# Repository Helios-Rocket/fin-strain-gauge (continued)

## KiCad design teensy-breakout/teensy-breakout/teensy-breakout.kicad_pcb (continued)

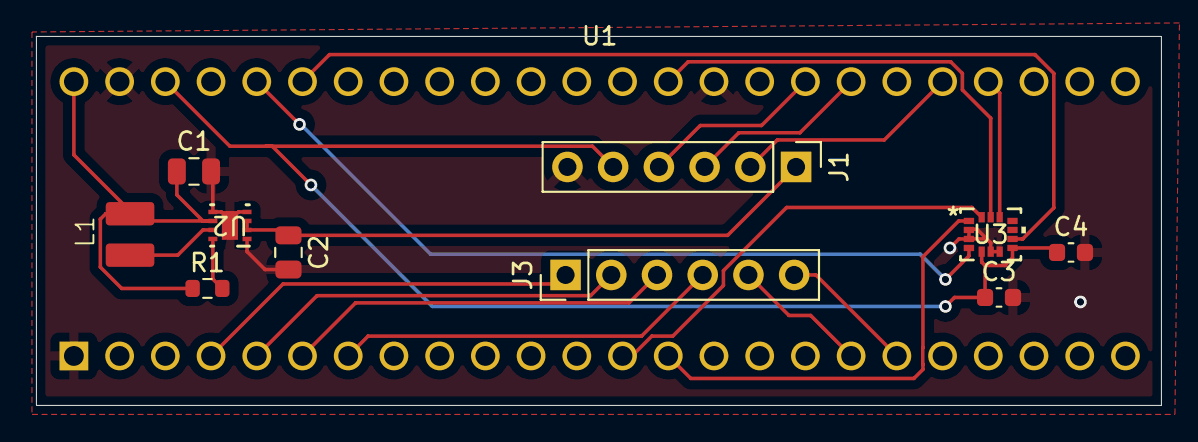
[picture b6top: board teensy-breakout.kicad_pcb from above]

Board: 2 copper layers, 62.5 x 20.5 mm, 11 parts (0 on the bottom side), 21 nets.

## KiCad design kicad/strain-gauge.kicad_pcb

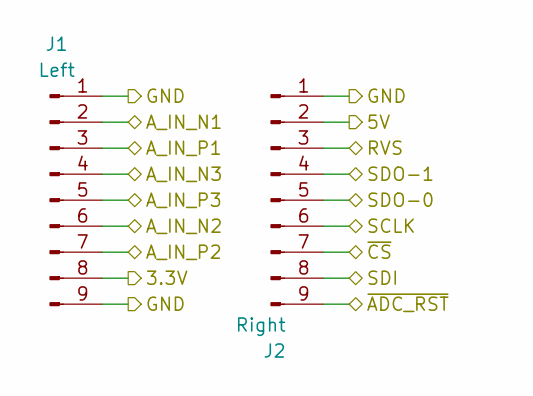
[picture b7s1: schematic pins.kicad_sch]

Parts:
J1: Left; PinHeader_1x09_P1.00mm_Vertical
J2: Right; PinHeader_1x09_P1.00mm_Vertical

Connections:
+3.3V: J1.8; also elsewhere on the board
+5V: J2.2; also elsewhere on the board
/ADC/RVS: J2.3; also elsewhere on the board
/ADC/SCLK: J2.6; also elsewhere on the board
/ADC/SDI: J2.8; also elsewhere on the board
/ADC/SDO-0: J2.5; also elsewhere on the board
/ADC/SDO-1: J2.4; also elsewhere on the board
/ADC/~CS: J2.7; also elsewhere on the board
/ADC/~RST: J2.9; also elsewhere on the board
/Multiplexer/A_IN_N1: J1.2; also elsewhere on the board
/Multiplexer/A_IN_N2: J1.6; also elsewhere on the board
/Multiplexer/A_IN_N3: J1.4; also elsewhere on the board
/Multiplexer/A_IN_P1: J1.3; also elsewhere on the board
/Multiplexer/A_IN_P2: J1.7; also elsewhere on the board
/Multiplexer/A_IN_P3: J1.5; also elsewhere on the board
GND: J1.1, J1.9, J2.1; also elsewhere on the board

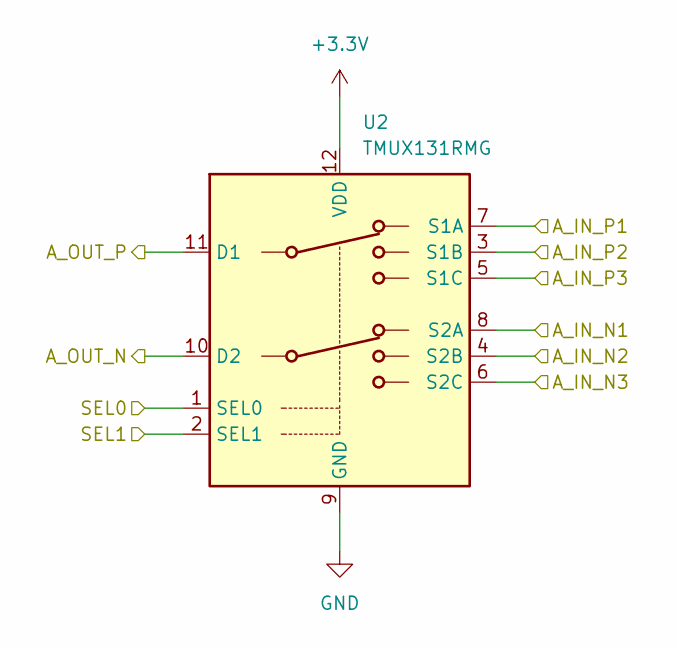
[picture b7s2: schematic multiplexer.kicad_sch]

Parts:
U2: TMUX131RMG; Texas_RMG0012A_WQFN-12_1.8x1.8mm_P0.4mm

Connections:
+3.3V: U2.12 (VDD); also elsewhere on the board
/Amplifier/A_IN_N: U2.10 (D2); also elsewhere on the board
/Amplifier/A_IN_P: U2.11 (D1); also elsewhere on the board
/Counter/SEL0: U2.1 (SEL0); also elsewhere on the board
/Counter/SEL1: U2.2 (SEL1); also elsewhere on the board
/Multiplexer/A_IN_N1: U2.8 (S2A); also elsewhere on the board
/Multiplexer/A_IN_N2: U2.4 (S2B); also elsewhere on the board
/Multiplexer/A_IN_N3: U2.6 (S2C); also elsewhere on the board
/Multiplexer/A_IN_P1: U2.7 (S1A); also elsewhere on the board
/Multiplexer/A_IN_P2: U2.3 (S1B); also elsewhere on the board
/Multiplexer/A_IN_P3: U2.5 (S1C); also elsewhere on the board
GND: U2.9 (GND); also elsewhere on the board

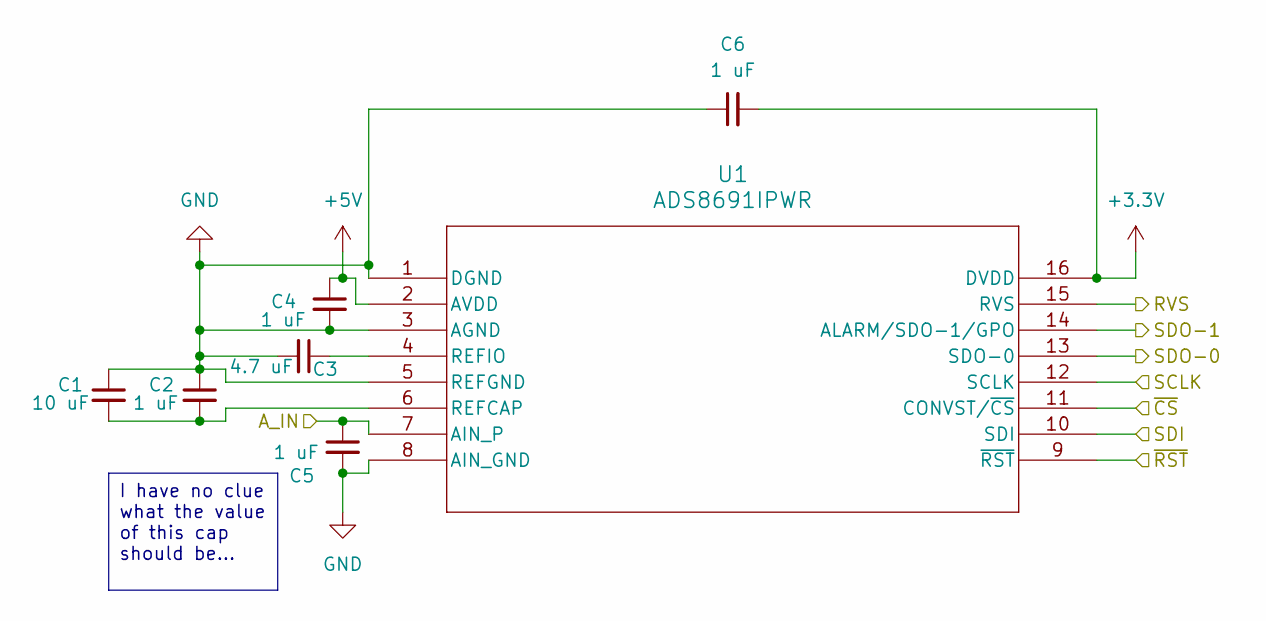
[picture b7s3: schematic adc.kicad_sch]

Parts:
C1: 10 uF; C_0805_2012Metric
C2, C4, C5, C6: 1 uF; C_0603_1608Metric
C3: 4.7 uF; C_0603_1608Metric
U1: ADS8691IPWR; PW16_TEX

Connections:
+3.3V: C6.2, U1.16 (DVDD); also elsewhere on the board
+5V: C4.1, U1.2 (AVDD); also elsewhere on the board
/ADC/A_IN: C5.1, U1.7 (AIN_P); also elsewhere on the board
/ADC/RVS: U1.15 (RVS); also elsewhere on the board
/ADC/SCLK: U1.12 (SCLK); also elsewhere on the board
/ADC/SDI: U1.10 (SDI); also elsewhere on the board
/ADC/SDO-0: U1.13 (SDO-0); also elsewhere on the board
/ADC/SDO-1: U1.14 (ALARM/SDO-1/GPO); also elsewhere on the board
/ADC/~CS: U1.11 (CONVST/~CS); also elsewhere on the board
/ADC/~RST: U1.9 (~RST); also elsewhere on the board
GND: C1.1, C2.1, C3.2, C4.2, C5.2, C6.1, U1.1 (DGND), U1.3 (AGND), U1.5 (REFGND), U1.8 (AIN_GND); also elsewhere on the board
unnamed: C1.2, C2.2, U1.6 (REFCAP)
unnamed: C3.1, U1.4 (REFIO)

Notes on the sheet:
I have no clue what the value of this cap should be...

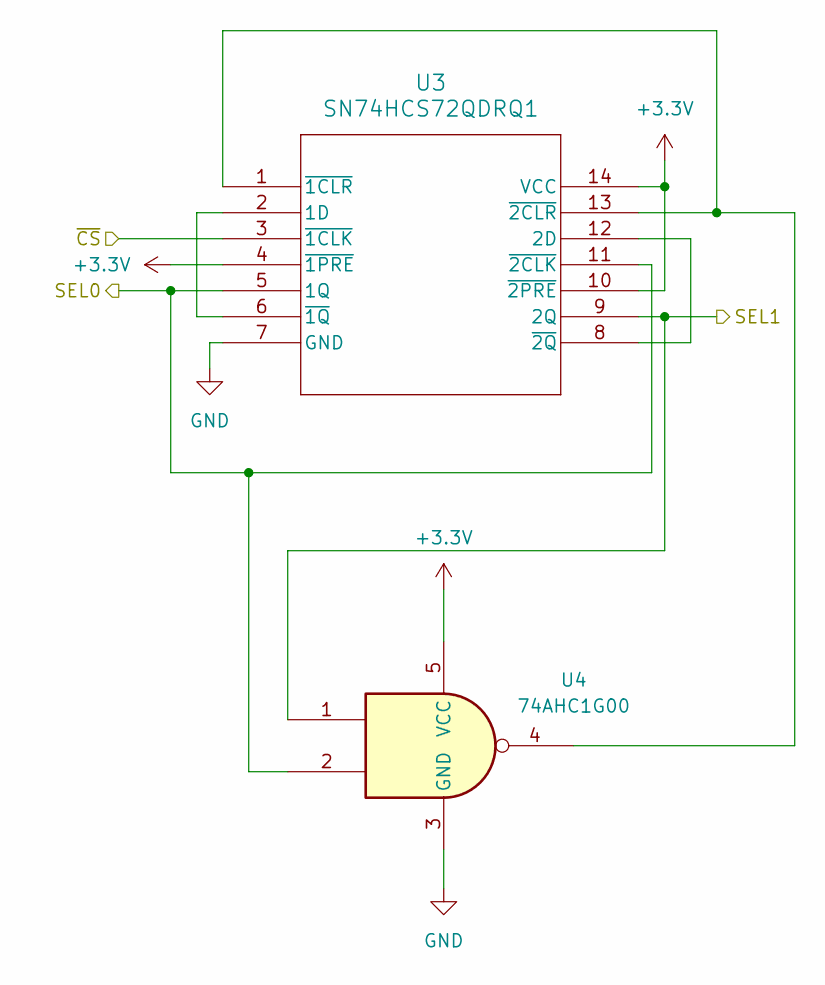
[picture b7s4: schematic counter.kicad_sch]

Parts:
U3: SN74HCS72QDRQ1; SOIC_QDRQ1_TEX
U4: 74AHC1G00; SOT-353_SC-70-5

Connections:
+3.3V: U3.4 (~1PRE), U3.10 (~2PRE), U3.14 (VCC), U4.5 (VCC); also elsewhere on the board
/ADC/~CS: U3.3 (~1CLK); also elsewhere on the board
/Counter/SEL0: U3.5 (1Q), U3.11 (~2CLK), U4.2; also elsewhere on the board
/Counter/SEL1: U3.9 (2Q), U4.1; also elsewhere on the board
GND: U3.7 (GND), U4.3 (GND); also elsewhere on the board
unnamed: U3.2 (1D), U3.6 (~1Q)
unnamed: U3.8 (~2Q), U3.12 (2D)
unnamed: U3.1 (~1CLR), U3.13 (~2CLR), U4.4

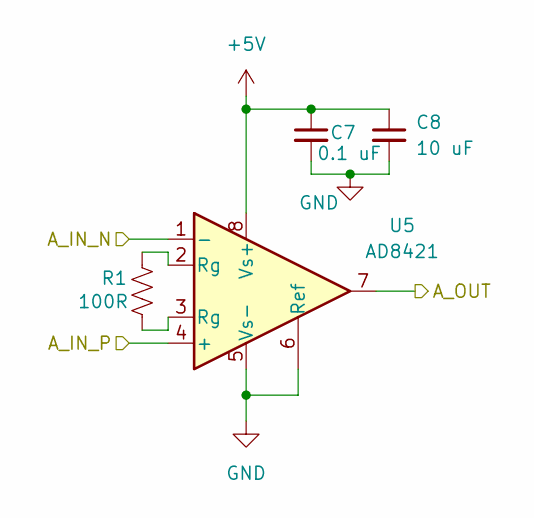
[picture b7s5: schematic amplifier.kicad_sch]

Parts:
C7: 0.1 uF; C_0603_1608Metric
C8: 10 uF; C_0805_2012Metric
R1: 100R; R_0603_1608Metric
U5: AD8421; MSOP-8_3x3mm_P0.65mm

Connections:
+5V: C7.1, C8.1, U5.8 (Vs+); also elsewhere on the board
/ADC/A_IN: U5.7; also elsewhere on the board
/Amplifier/A_IN_N: U5.1 (-); also elsewhere on the board
/Amplifier/A_IN_P: U5.4 (+); also elsewhere on the board
GND: C7.2, C8.2, U5.5 (Vs-), U5.6 (Ref); also elsewhere on the board
unnamed: R1.1, U5.2 (Rg)
unnamed: R1.2, U5.3 (Rg)

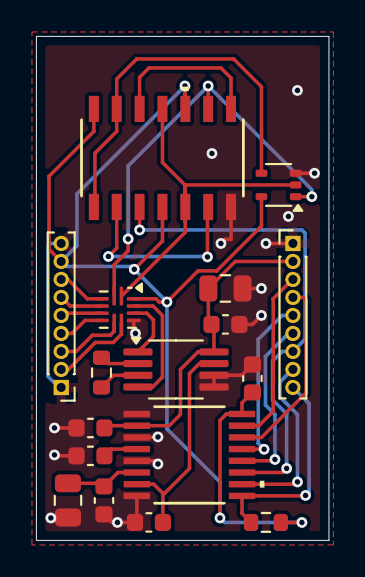
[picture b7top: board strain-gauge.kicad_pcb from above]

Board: 2 copper layers, 16.2 x 28.0 mm, 17 parts (0 on the bottom side), 28 nets.

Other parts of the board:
R2: 100k; R_0603_1608Metric

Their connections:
+3.3V: R2.2; also elsewhere on the board
/ADC/~RST: R2.1; also elsewhere on the board

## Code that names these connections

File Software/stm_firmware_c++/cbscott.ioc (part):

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Mcu.Name=STM32L412C8Tx
Mcu.Package=LQFP48
Mcu.UserName=STM32L412C8Tx
PA0.Signal=S_TIM2_CH1
PA1.Mode=Full_Duplex_Master
PA1.Signal=SPI1_SCK
PA10.Mode=Asynchronous
PA10.Signal=USART1_RX
PA11.Mode=Full_Duplex_Master
PA11.Signal=SPI1_MISO
PA12.Mode=Full_Duplex_Master
PA12.Signal=SPI1_MOSI
PA13\ (JTMS/SWDIO).Mode=Serial_Wire
PA13\ (JTMS/SWDIO).Signal=SYS_JTMS-SWDIO
PA14\ (JTCK/SWCLK).Mode=Serial_Wire
PA14\ (JTCK/SWCLK).Signal=SYS_JTCK-SWCLK
PA2.Mode=Single Bank 1
PA2.Signal=QUADSPI_BK1_NCS
PA3.Mode=Single Bank 1
PA3.Signal=QUADSPI_CLK
PA4.GPIOParameters=GPIO_Label
PA4.GPIO_Label=SPI1_CS
PA4.Signal=GPIO_Output
PA6.Mode=Single Bank 1
PA6.Signal=QUADSPI_BK1_IO3
PA7.Mode=Single Bank 1
PA7.Signal=QUADSPI_BK1_IO2
PA9.Mode=Asynchronous
PA9.Signal=USART1_TX
PB0.Mode=Single Bank 1
PB0.Signal=QUADSPI_BK1_IO1
PB1.Mode=Single Bank 1
PB1.Signal=QUADSPI_BK1_IO0
PB10.GPIOParameters=GPIO_Label
PB10.GPIO_Label=SIGNAL
PB10.Signal=GPIO_Input
PB11.GPIOParameters=GPIO_Label
PB11.GPIO_Label=AVBAY_SYNC
PB11.Signal=GPIO_Output
PB12.GPIOParameters=GPIO_Label
PB12.GPIO_Label=ADC_CS
PB12.Signal=GPIO_Output
PB13.Mode=Full_Duplex_Master
PB13.Signal=SPI2_SCK
PB14.Mode=Full_Duplex_Master
PB14.Signal=SPI2_MISO
PB15.Mode=Full_Duplex_Master
PB15.Signal=SPI2_MOSI
PB5.GPIOParameters=GPIO_Label
PB5.GPIO_Label=STATUS_LED
PB5.Signal=GPIO_Output
PB8.GPIOParameters=GPIO_Label
PB8.GPIO_Label=ADC_DRDY
PB8.Signal=GPIO_Input
PB9.GPIOParameters=GPIO_Label
PB9.GPIO_Label=ADC_RST
PB9.Signal=GPIO_Output
RCC.HSE_VALUE=8000000
RCC.SYSCLKFreq_VALUE=48000000
board=custom

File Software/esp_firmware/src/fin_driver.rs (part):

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        pcnt: PCNT<'d>,
        fin0_rx: AnyPin<'d>,
        fin0_tx: AnyPin<'d>,
        fin1_rx: AnyPin<'d>,
        fin1_tx: AnyPin<'d>,
        fin2_rx: AnyPin<'d>,
        fin2_tx: AnyPin<'d>,
        fin3_rx: AnyPin<'d>,
        fin3_tx: AnyPin<'d>,
    ) -> Result<(Self, FinsIdle), FinCommsError> {
        let mut this = Self {
            raw_pins: [
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
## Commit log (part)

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2025-06-22 add kicad project
2025-06-23 first pass at testing board schematic, except amplifier wiring
2025-06-24 finish schematic for amp, and start routing (schematic isn't actually fully connected yet tho...)
2025-06-24 started routing pcb
2025-06-24 the routing is awful but also done
2025-06-24 make the component values more visible on pcb
2025-06-24 slightly better routing
2025-07-02 moved traces
2025-07-02 small fixes
2025-07-02 redo routing with correct header pin footprint
2025-07-28 kicad is very strainfull
2025-08-02 added schematic to new SGTC
2025-08-03 redo schematic for fin board
2025-08-03 fin center draft
2025-08-03 silkscreen things mostly
2025-08-03 strain gauge fix
2025-08-10 final version
2025-08-10 added teensy schematic
2025-08-10 routing go brrr
2025-08-18 oops I wasn't commiting... implement beginning of sd card driver + (hopefully) the clock for the adc
2025-08-20 flex pwm working :D
2025-08-23 adc reading but not well
2025-08-24 types go brr (this change is completely untested, but does compile...)
2025-08-25 start of esp32 flight computer schematic
2025-08-27 started pcb
2025-08-29 added global library
2025-08-29 more routing and laying out of board
2025-08-31 moved methods around
2025-09-01 reading temperature data works! (with mystery multiplication by 2)
2025-09-02 fixed couple things
2025-09-03 some more routing for the esp board
2025-09-07 finish general board layout. Needs some silkscreen fixing
2025-09-07 fixed core dimensions and pin locations
2025-09-07 switch out inductor and some caps
2025-09-09 add/fix 3d models
2025-09-09 Fix button footprints
2025-09-09 switch passive values on esp32 enable pin to be ones we already use
2025-09-09 add decoupling cap right next to esp32
2025-09-10 added new esp firmware
2025-09-13 setup reading strain gauge
2025-09-15 update fins with bridge completion resistors
2025-09-15 finishing(?) touches on flight computer board
2025-09-16 update RC filter values
2025-09-28 change some pins around
2025-09-28 gerbers
2025-09-28 add crc check
2025-10-01 change pins around
2025-10-01 add esp project
2025-10-01 something on the teensy
2025-10-01 added initial SPI
2025-10-01 fix some things
2025-10-01 read axis
2025-10-03 use Format instead of Debug
2025-10-08 change print logic
2025-10-09 correct adc code to volt calculations
2025-10-13 changes for working with all four fins
2025-10-24 sd initialization + fin code ported to esp32 (untested)
2025-10-25 fix reading adc data
2025-11-02 remake boards better with four layers
2025-11-04 added current sensor stuff and rerouted fc
2025-11-05 finished connecting things
2025-11-05 fix read_reg to use correct bytes
2025-11-05 fixed?
2025-11-05 small fixups
2025-11-05 fix gerbers
2025-11-05 make board 4 layers instead of 6
2025-11-09 temp commit while working on sd card
2025-11-09 sending working
2025-11-12 sd reading works
2025-11-12 add random delay to fix command timeout
2025-11-13 wifi folder working
2025-11-19 updated sd code
2025-11-22 changed seek and read
2025-11-22 fix writing to fifo
2025-11-22 configure lsm registers
2025-11-22 fix weird merge things
2025-11-22 handle lsm chip select externally from peripheral
2025-11-22 imu set up
2025-12-04 actually use the reset pin and enable the fins
2025-12-24 started organizing
2025-12-25 more cleaning
2025-12-26 setup libraries
2025-12-26 start pin assignments
2025-12-26 added new STM chip
2025-12-27 finished schematic
2025-12-27 prettify schematic a bit
2025-12-29 start placing components
2025-12-31 place more components and silkscreen
2026-01-01 all traces but test points
2026-01-01 fixed some traces, placed test points in initial positions
2026-01-01 finished routing test points and fixed all build errors
2026-01-01 finish up silkscreen
2026-01-01 Revert "place more components and silkscreen"
    This reverts commit 1bc8328d4b62153ca3fb5bb472924e08519ee507.
2026-01-02 touchup a few things
2026-01-02 generate fin prototype fab outputs
2026-03-21 rename and delete old firmware
2026-03-21 added in stm c++ code
2026-03-21 update flake for nix development
2026-03-21 basic stm rust setup
2026-03-21 it blink!
2026-03-21 Added in old spi code
2026-03-21 spi kinda working but not really
2026-04-01 fix spi and read flash status regs
